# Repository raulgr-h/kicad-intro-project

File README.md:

# Kicad Intro Project

We will be creating an Astable timer circuit using a 555 timer, an LED, resistors, capacitors, and batteries. 555 timers can be used to generate stable and accurate oscillations or time delays. In our case, we will be using this [timer](https://www.ti.com/lit/ds/symlink/lm555.pdf?HQS=dis-dk-null-digikeymode-dsf-pf-null-wwe&ts=1630736989538&ref_url=https%253A%252F%252Fwww.ti.com%252Fgeneral%252Fdocs%252Fsuppproductinfo.tsp%253FdistId%253D10%2526gotoUrl%253Dhttps%253A%252F%252Fwww.ti.com%252Flit%252Fgpn%252Flm555) to run in Astable operation mode, which means that it will begin a free running oscillation. I recommend reading through the datasheet linked above, as lots of useful information can be found there! The frequency of the oscillations can be controlled by the value of resistors and capacitors that you choose to use in your circuit.  

The equation used to calculate the frequency is shown here:

## Create a new Kicad Project:
+ The documentation for Kicad can be found [here](https://docs.kicad.org/5.1/en/getting_started_in_kicad/getting_started_in_kicad.html), where there is a step-by-step tutorial on creating your first project.
+ Create a new project by clicking File->New->Project, and naming it.

## Create your schematic:
+ The first step to designing a PCB is creating the schematic. Open the Kicad Schematic software, “Eeschema”, by clicking on the button titled “Schematic Layout Editor”. Now you can begin to create your circuit!
+ There wil also be an example schematic included in the repository that can be used as a reference.
+ Begin placing components and wiring them together to create the circuit. Refer back to the [Kicad documentation](https://docs.kicad.org/5.1/en/getting_started_in_kicad/getting_started_in_kicad.html) for detailed instructions on how to place components and connect them together. All of  the components necessary for this tutorial are available in the Kicad component library. A list of the components you will need:
    + *1* LM555 Timer
    + *1* LED
    + *2* Resistors(1 10k Resistor, and 1 5k Resistor)
    + *2* Capacitors(1 0.01uF Capacitor, and 1 10uF Capacitor)
    + *2* 3V Single Cell Batteries
    + *2* VCC Labels
    + *2* GND Labels
    + *2* Power Flags
+  An example circuit for an Astable timer can be found in the datasheet(not including batteries):

+ Once you have finished making your circuit, run through these steps in order:
    1. Click on the Annotate Schematic symbol , and annotate all symbols in the schematic.
    2. Click on the Electrical Rules Check(ERC) symbol , and verify that you aren't violating any electrical rules.
    3. Click on the Assign PCB footprints to schematic symbol . Here, you will tell the PCB editor which physical footprint goes with each schematic symbol. It is up to you to make sure that the symbol has the corresponding footprint. The list of footprints that will be used:
        + *2* Battery:BatteryHolder_LINX_BAT-HLD-012-SMT
        + *2* Capacitor_SMD:C_0805_2012Metric
        + *2* Resistor_SMD:R_0805_2012Metric
        + *1* LED_SMD:LED_0805_2012Metric
        + *1* Package_SO:SOIC-8_3.9x4.9mm_P1.27mm (for the 555 timer)
    4. Click on the Generate Netlist symbol , and generate the netlist that will be used in the PCB editor, "PCBnew".
+ You have now finished with the Schematic design part of this project! Next, we will complete the PCB design in PCBnew

## Create your PCB Layout
+ Again, refer back to the [Kicad documentation](https://docs.kicad.org/5.1/en/getting_started_in_kicad/getting_started_in_kicad.html) for more detailed instructions on how to create a PCB Layout.
+ Click on the Pcbnew symbol  that will take you to the PCB editor.
+ We will be creating a two layer board, which is the default in Kicad. We will also be keeping the default track width and PCB thickness.
+ To load in the netlist that was previously generated, click on the same Load Netlist symbol . Find the netlist file that was generated and then click Update PCB. This will place all of the components on the page with a ratsnest connecting all the pins. You can move components around until you have a very rough initial layout. This does not have to be your final component placement, their position can always be moved.
+ To create a physical border for the PCB, make sure you have clicked on the layer labeled Edge.Cuts, and create a rectangle or square using the Graphic Polygon tool 
+ Make sure all of your components are inside your board outline, and then begin routing tracks between the different pins on your components. Once all the white lines of the ratsnest have disappeared, you'll know that all your components have been fully connected. Routing between many components can be challenging, don't be afraid to try mutliple paths until you are satisfied with your layout. Feel free to route on both sides of the board using vias if necessary.
+ Run the ERC  again to make sure everything is connected.
+ You can add text to both the front and back layers of your board by clicking on the Add Text symbol  and the corresponding layer, either F.SilkS or B.SilkS. The convention for boards is to include the title of the board, the designer's name, and the revision number.
+ Kicad allows you to view a 3D version of your board! Go to View->3D Viewer to see a 3D rendering.
+ Once you have finalized your layout, you can generate the Gerber files that will be uploaded to a PCB manufacturer's website. Click on the Plot symbol  and generate Gerber files in the folder of your choice. If you have mounting holes or vias on your board, generate the drill files as well.
+ You have completed the PCB design section of this project!
+ If interested, your PCB can possibly be ordered from JLCPCB and hand-soldered together. This is not a required part of the intro project.

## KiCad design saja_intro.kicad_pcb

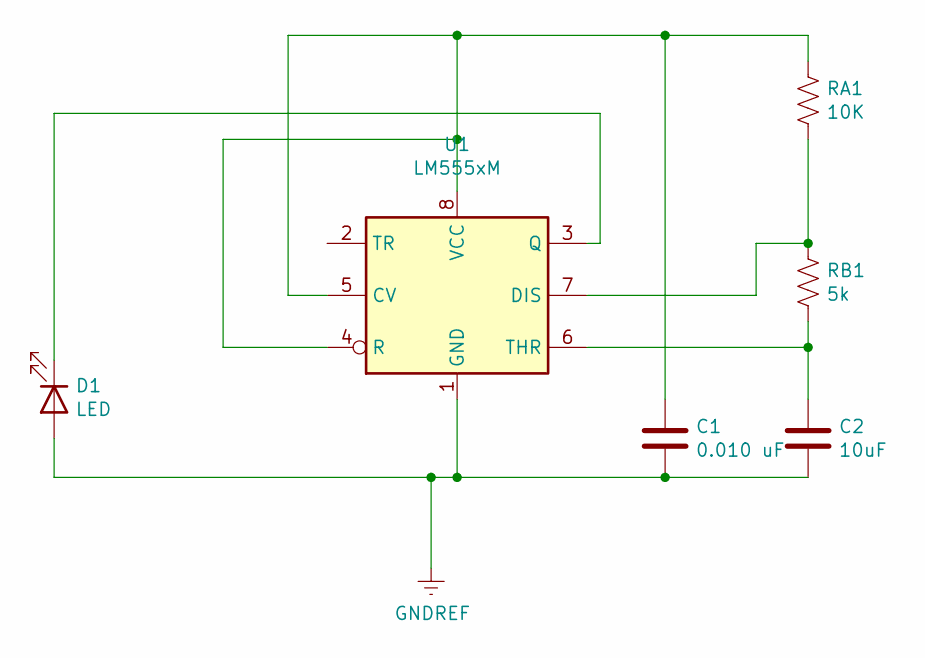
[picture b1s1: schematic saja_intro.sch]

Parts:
C1: 0.010 uF; C_0805_2012Metric
C2: 10uF; C_0805_2012Metric
D1: LED; LED_0805_2012Metric
RA1: 10K; R_0805_2012Metric
RB1: 5k; R_0805_2012Metric
U1: LM555xM; SOIC-8_3.9x4.9mm_P1.27mm

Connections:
GNDREF: C1.2, C2.2, D1.2 (A), U1.1 (GND)
unnamed: C1.1, RA1.1, U1.4 (R), U1.5 (CV), U1.8 (VCC)
unnamed: C2.1, RB1.2, U1.6 (THR)
unnamed: D1.1 (K), U1.3 (Q)
unnamed: RA1.2, RB1.1, U1.7 (DIS)

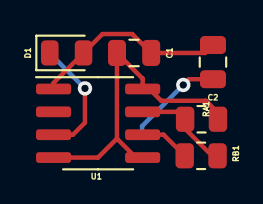
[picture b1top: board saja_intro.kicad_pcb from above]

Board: 2 copper layers, 6 parts (0 on the bottom side), 5 nets.

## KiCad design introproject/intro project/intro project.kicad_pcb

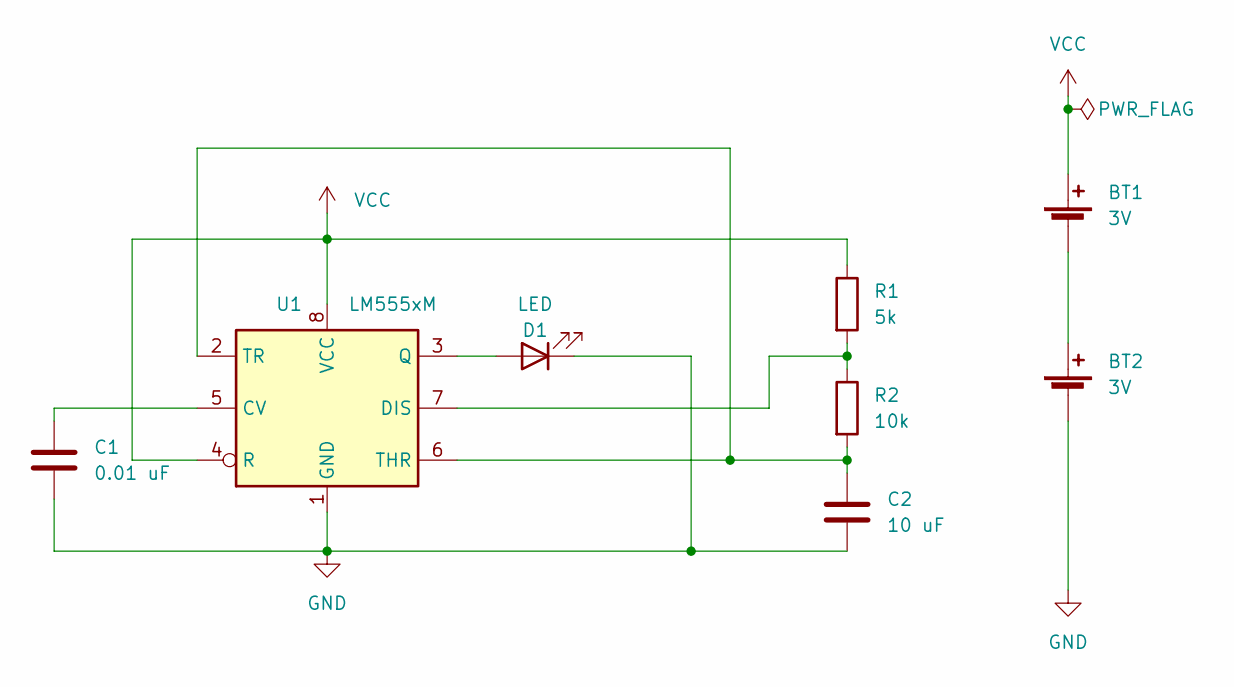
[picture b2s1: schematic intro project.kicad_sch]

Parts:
BT1, BT2: 3V; BatteryHolder_LINX_BAT-HLD-012-SMT
C1: 0.01 uF; C_0805_2012Metric
C2: 10 uF; C_0805_2012Metric
D1: LED; LED_0805_2012Metric
R1: 5k; R_0805_2012Metric
R2: 10k; R_0805_2012Metric
U1: LM555xM; SOIC-8_3.9x4.9mm_P1.27mm

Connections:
GND: BT2.2 (-), C1.2, C2.2, D1.1 (K), U1.1 (GND)
unnamed: BT1.2 (-), BT2.1 (+)
unnamed: C1.1, U1.5 (CV)
unnamed: C2.1, R2.2, U1.2 (TR), U1.6 (THR)
unnamed: D1.2 (A), U1.3 (Q)
unnamed: R1.2, R2.1, U1.7 (DIS)
VCC: BT1.1 (+), R1.1, U1.4 (R), U1.8 (VCC)

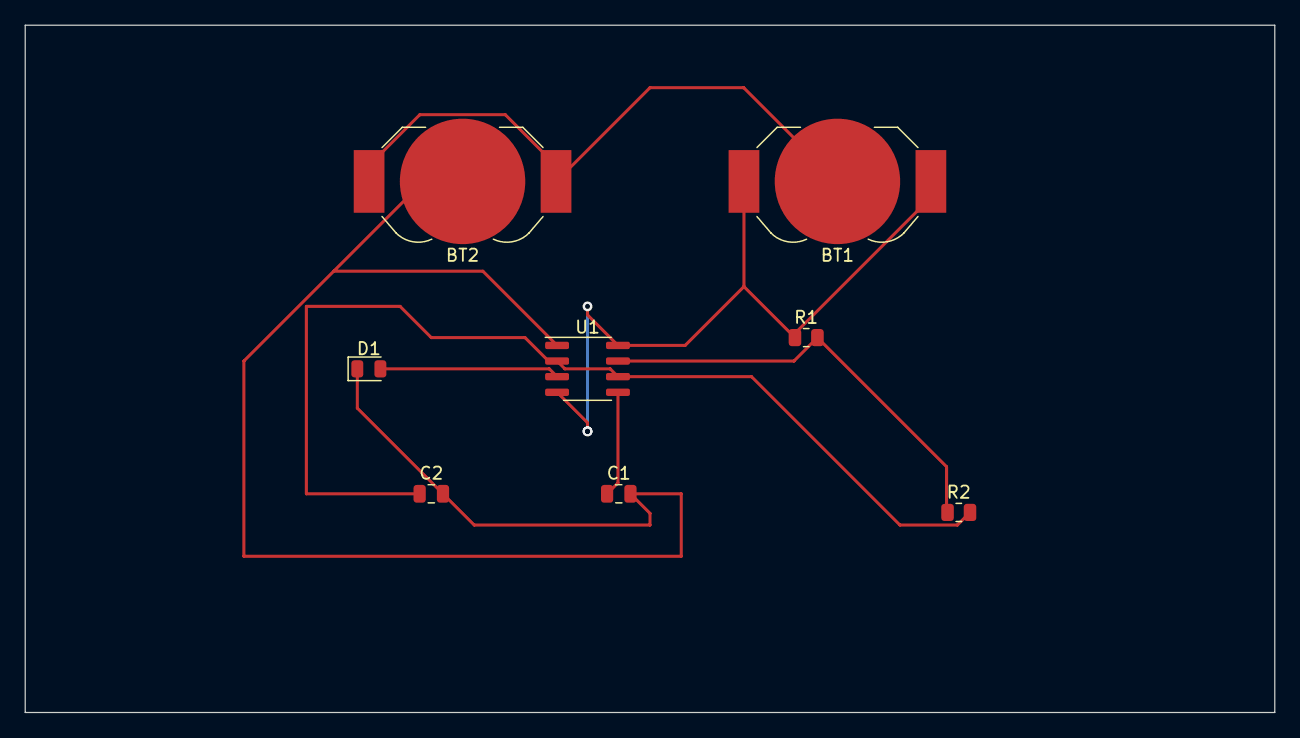
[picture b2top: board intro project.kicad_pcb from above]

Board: 2 copper layers, 101.6 x 55.9 mm, 8 parts (0 on the bottom side), 7 nets.

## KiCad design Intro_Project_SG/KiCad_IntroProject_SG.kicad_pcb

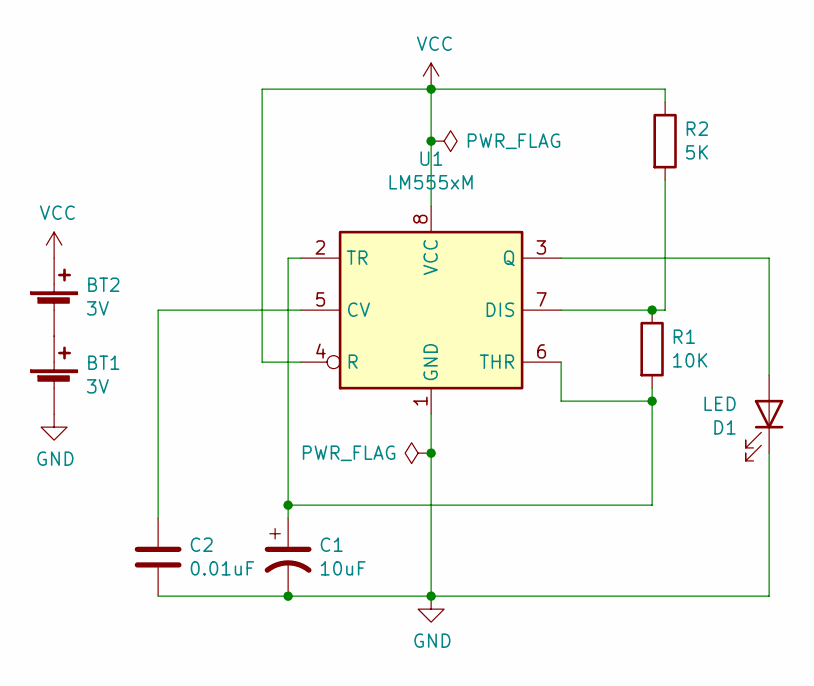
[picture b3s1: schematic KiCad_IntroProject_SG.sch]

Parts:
BT1, BT2: 3V; BatteryHolder_LINX_BAT-HLD-012-SMT
C1: 10uF; C_0805_2012Metric
C2: 0.01uF; C_0805_2012Metric
D1: LED; LED_0805_2012Metric
R1: 10K; R_0805_2012Metric
R2: 5K; R_0805_2012Metric
U1: LM555xM; SOIC-8_3.9x4.9mm_P1.27mm

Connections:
GND: BT1.2 (-), C1.2, C2.2, D1.1 (K), U1.1 (GND)
unnamed: BT1.1 (+), BT2.2 (-)
unnamed: C1.1, R1.2, U1.2 (TR), U1.6 (THR)
unnamed: C2.1, U1.5 (CV)
unnamed: D1.2 (A), U1.3 (Q)
unnamed: R1.1, R2.2, U1.7 (DIS)
VCC: BT2.1 (+), R2.1, U1.4 (R), U1.8 (VCC)

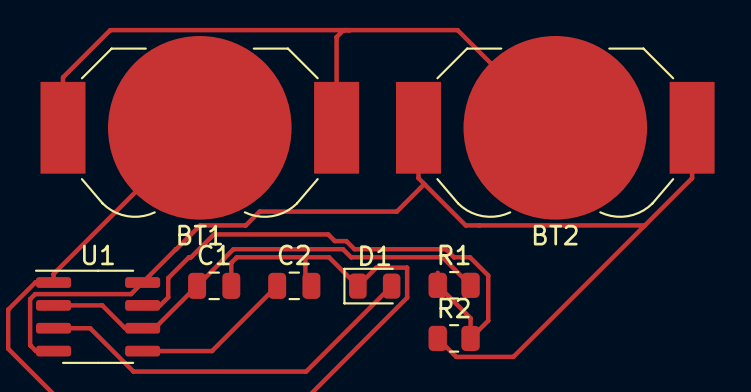
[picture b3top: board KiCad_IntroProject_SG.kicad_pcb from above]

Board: 2 copper layers, 8 parts (0 on the bottom side), 7 nets.

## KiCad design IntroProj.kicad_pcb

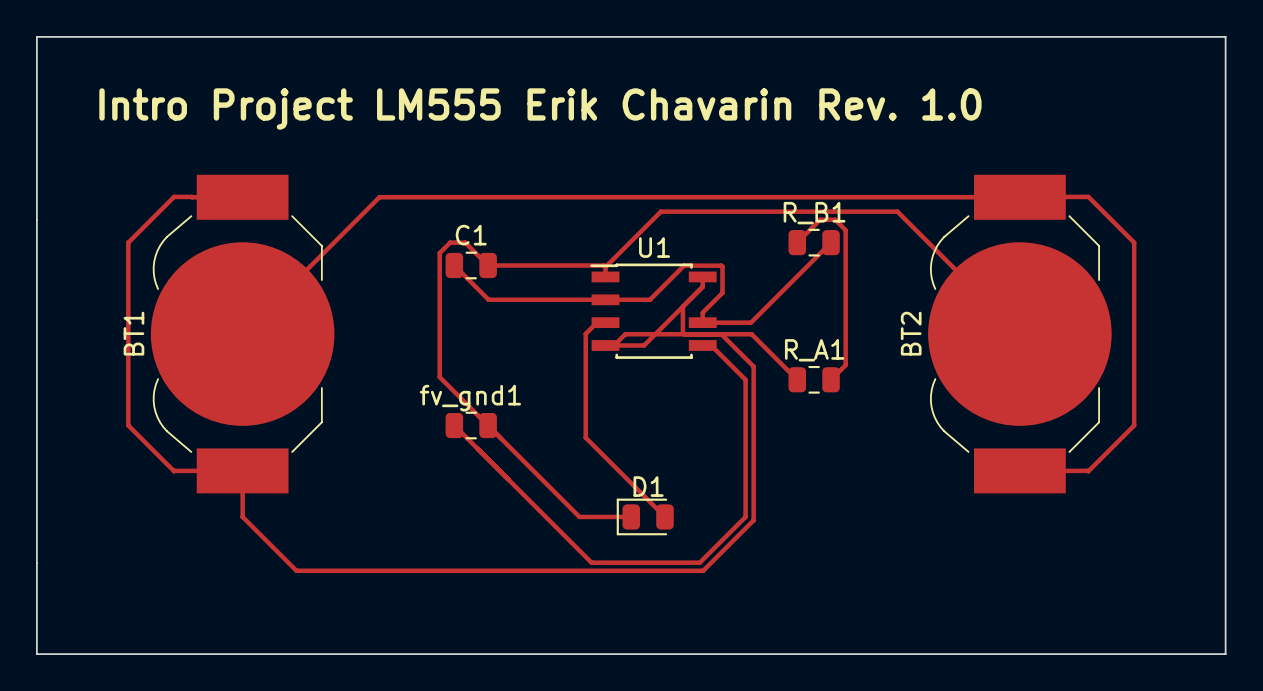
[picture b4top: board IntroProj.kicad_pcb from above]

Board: 2 copper layers, 66.0 x 34.3 mm, 8 parts (0 on the bottom side), 7 nets.

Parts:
BT1, BT2: Battery_Cell; BatteryHolder_LINX_BAT-HLD-012-SMT
C1: 10u; C_0805_2012Metric
D1: LED; LED_0805_2012Metric
R_A1: 5k; R_0805_2012Metric
R_B1: 10k; R_0805_2012Metric
U1: LM555; SOIC-8-N7_3.9x4.9mm_P1.27mm
fv_gnd1: 0.01u; C_0805_2012Metric

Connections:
GND: BT2.2, C1.2, D1.1, U1.1, fv_gnd1.2
unnamed: BT1.2, BT2.1
unnamed: C1.1, R_B1.2, U1.2, U1.6
unnamed: D1.2, U1.3
unnamed: R_A1.2, R_B1.1
unnamed: U1.5, fv_gnd1.1
VCC: BT1.1, R_A1.1, U1.4, U1.8

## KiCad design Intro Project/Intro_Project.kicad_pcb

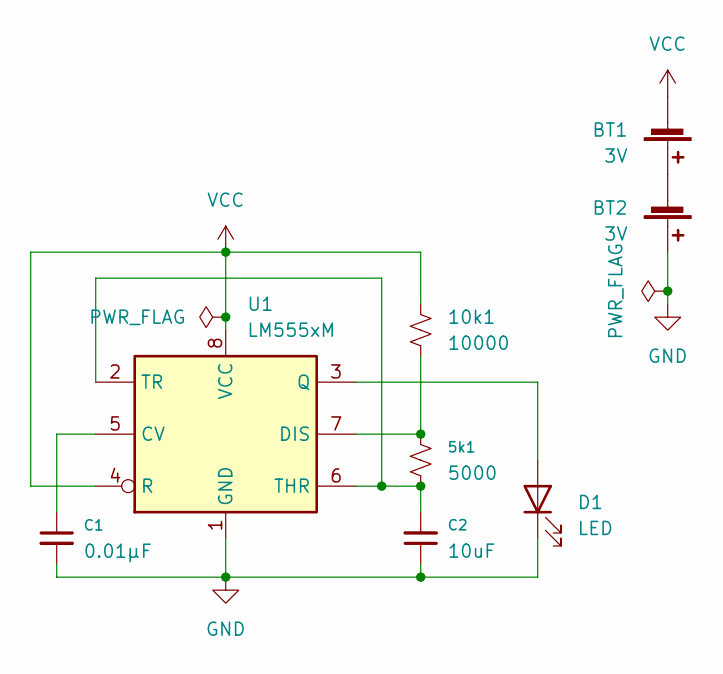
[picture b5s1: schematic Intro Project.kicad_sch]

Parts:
5k1: 5000; R_0805_2012Metric
10k1: 10000; R_0805_2012Metric
BT1, BT2: 3V; BatteryHolder_LINX_BAT-HLD-012-SMT
C1: 0.01µF; C_0805_2012Metric
C2: 10uF; C_0805_2012Metric
D1: LED; LED_0805_2012Metric
U1: LM555xM; SOIC-8_3.9x4.9mm_P1.27mm

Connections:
GND: BT2.1 (+), C1.2, C2.1, D1.1 (K), U1.1 (GND)
unnamed: 5k1.1, 10k1.2, U1.7 (DIS)
unnamed: BT1.1 (+), BT2.2 (-)
unnamed: C1.1, U1.5 (CV)
unnamed: 5k1.2, C2.2, U1.2 (TR), U1.6 (THR)
unnamed: D1.2 (A), U1.3 (Q)
VCC: 10k1.1, BT1.2 (-), U1.4 (R), U1.8 (VCC)

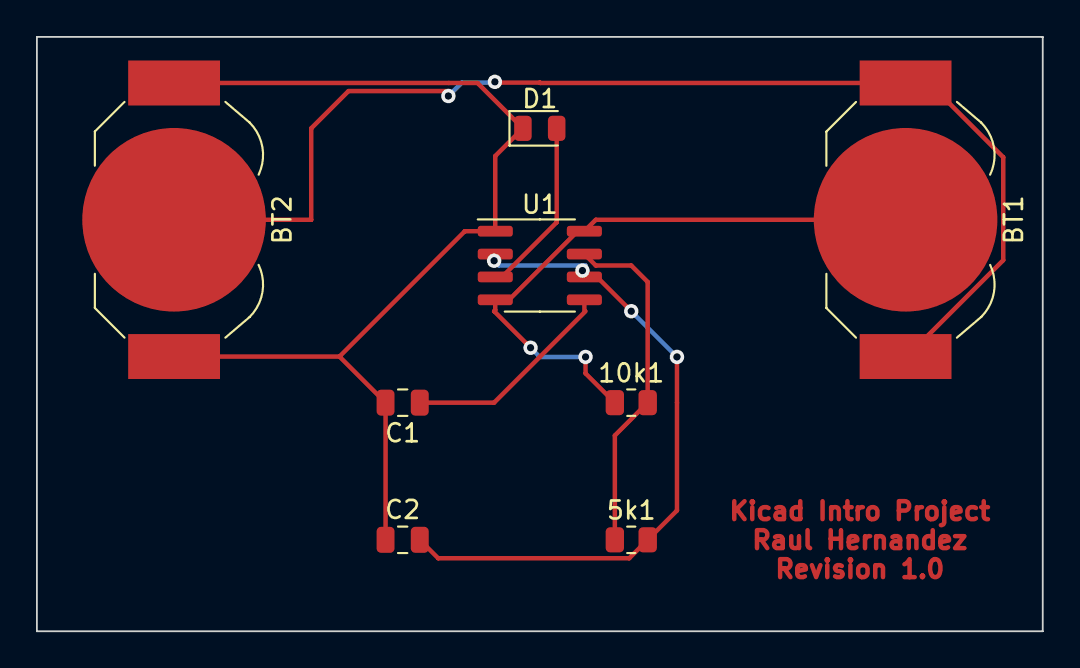
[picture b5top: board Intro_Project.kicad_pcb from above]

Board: 2 copper layers, 55.9 x 33.0 mm, 8 parts (0 on the bottom side), 7 nets.

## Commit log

2021-09-04 Add image for README
2021-09-04 Add schematic image example
2021-09-04 Add kicad symbol images
2021-09-04 Add pcbnew icon image
2021-09-04 Add pcbnew text and plot images
2021-09-04 Add detailed instructions to README.md
2021-09-04 Add example Kicad Intro Project
2021-09-16 Get rid of condescending words
2021-09-23 add blake intro project
2021-09-23 add intro project
2021-09-23 add Tomas intro project
2021-09-23 Added Intro Project
2021-09-23 schematic finished
2021-09-27 Kicad Design and PCB
2021-09-28 Create file1
2021-09-28 Create file2
2021-09-29 This is my intro project
2021-10-01 Completed 555 Astable Timer Project.
2021-10-04 finished intro project
2022-03-02 Kicad Intro Project
2022-03-03 intro project commit
2022-03-20 Saja Intro First Commit
2022-10-02 Raul
